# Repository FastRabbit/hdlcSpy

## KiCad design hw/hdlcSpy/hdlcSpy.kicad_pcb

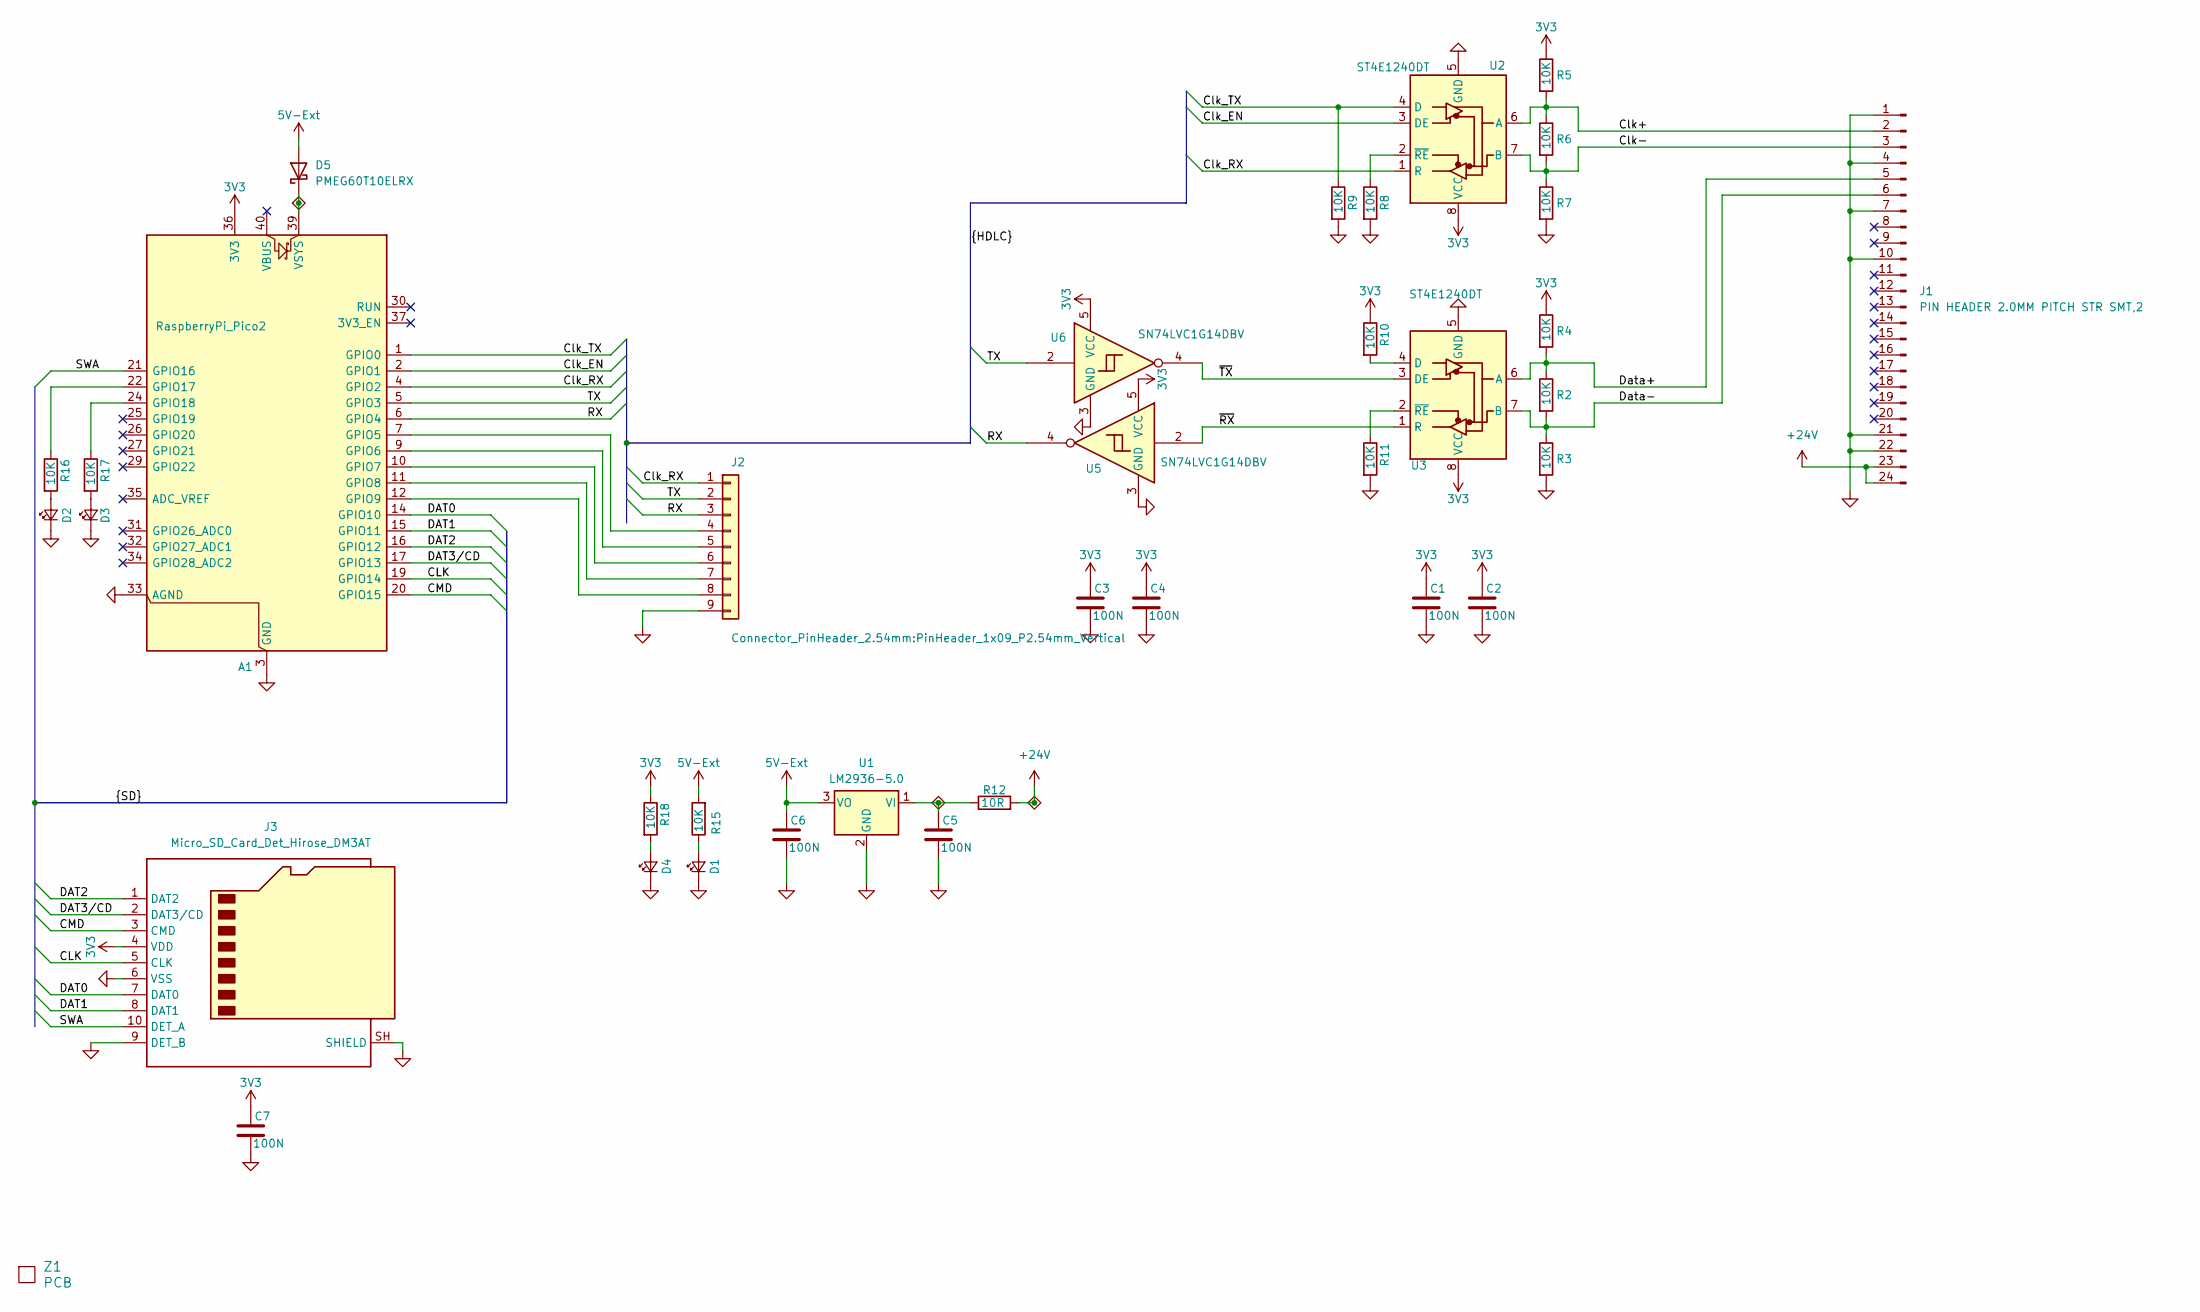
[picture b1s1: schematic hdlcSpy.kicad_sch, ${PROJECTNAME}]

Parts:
A1: RaspberryPi_Pico2; RaspberryPi_Pico_Common_Unspecified; DigiKey 2648-SC1631CT-ND
C1, C2, C3, C4, C5, C6, C7: 100N; C_0603_1608Metric_Pad1.08x0.95mm_HandSolder
D1, D2, D3, D4: VLMTG1400-GS08; LED_0603_1608Metric; DigiKey VLMTG1400-GS08CT-ND
D5: PMEG60T10ELRX; Nexperia_CFP3_SOD-123W; DigiKey 1727-7807-1-ND
J1: PIN HEADER 2.0MM PITCH STR SMT,2; G825M24401YEU; DigiKey 664-G825M24401YEUTR-ND
J2: Connector_PinHeader_2.54mm:PinHeader_1x09_P2.54mm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; PinHeader_1x09_P2.54mm_Vertical
J3: Micro_SD_Card_Det_Hirose_DM3AT; DM3CS-SF; Mouser 798-DM3D-SF
R2, R3, R4, R5, R6, R7, R8, R9, R10, R11, R15, R16, R17, R18: 10K; R_0603_1608Metric_Pad0.98x0.95mm_HandSolder
R12: 10R; R_0603_1608Metric_Pad0.98x0.95mm_HandSolder
U1: LM2936-5.0; SOT-223-3_TabPin2; DigiKey LM2936MP-5.0/NOPBCT-ND
U2, U3: ST4E1240DT; SOIC-8_3.9x4.9mm_P1.27mm; DigiKey 296-23802-1-ND
U5, U6: SN74LVC1G14DBV; SOT-23-5; DigiKey 296-11607-1-ND
Z1: PCB; 4L

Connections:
3V3: A1.36 (3V3), C1.1, C2.1, C3.1, C4.1, C7.1, J3.4 (VDD), R4.1, R5.1, R10.1, R18.1, U2.8 (VCC), U3.8 (VCC), U5.5 (VCC), U6.5 (VCC)
5V-Ext: C6.1, D5.2 (A), R15.2, U1.3 (VO)
+24V: J1.23, J1.24, R12.2
/CLK: A1.19 (GPIO14), J3.5 (CLK)
/CMD: A1.20 (GPIO15), J3.3 (CMD)
/Clk+: J1.2, R5.2, R6.1, U2.6 (A)
/Clk-: J1.3, R6.2, R7.1, U2.7 (B)
/Clk_EN: A1.2 (GPIO1), U2.3 (DE)
/Clk_RX: A1.4 (GPIO2), J2.1, U2.1 (R)
/Clk_TX: A1.1 (GPIO0), R9.1, U2.4 (D)
/DAT0: A1.14 (GPIO10), J3.7 (DAT0)
/DAT1: A1.15 (GPIO11), J3.8 (DAT1)
/DAT2: A1.16 (GPIO12), J3.1 (DAT2)
/DAT3/CD: A1.17 (GPIO13), J3.2 (DAT3/CD)
/Data+: J1.5, R2.1, R4.2, U3.6 (A)
/Data-: J1.6, R2.2, R3.1, U3.7 (B)
/RX: A1.6 (GPIO4), J2.3, U5.4
/SWA: A1.21 (GPIO16), J3.10 (DET_A)
/TX: A1.5 (GPIO3), J2.2, U6.2
/~RX: U3.1 (R), U5.2
/~TX: U3.3 (DE), U6.4
GND: A1.3 (GND), A1.8 (GND), A1.13 (GND), A1.18 (GND), A1.23 (GND), A1.28 (GND), A1.33 (AGND), A1.38 (GND), C1.2, C2.2, C3.2, C4.2, C5.2, C6.2, C7.2, D1.1 (K), D2.1 (K), D3.1 (K), D4.1 (K), J1.1, J1.4, J1.7, J1.10, J1.21, J1.22, J2.9, J3.6 (VSS), J3.9 (DET_B), J3.SH (SHIELD), R3.2, R7.2, R8.2, R9.2, R11.2, U1.2 (GND), U2.5 (GND), U3.5 (GND), U5.3 (GND), U6.3 (GND)
unnamed: A1.7 (GPIO5), J2.4
unnamed: A1.9 (GPIO6), J2.5
unnamed: A1.10 (GPIO7), J2.6
unnamed: A1.11 (GPIO8), J2.7
unnamed: A1.12 (GPIO9), J2.8
unnamed: A1.22 (GPIO17), R16.1
unnamed: A1.24 (GPIO18), R17.1
unnamed: A1.39 (VSYS), D5.1 (K)
unnamed: D1.2 (A), R15.1
unnamed: D2.2 (A), R16.2
unnamed: D3.2 (A), R17.2
unnamed: D4.2 (A), R18.2
unnamed: C5.1, R12.1, U1.1 (VI)
unnamed: R8.1, U2.2 (~RE)
unnamed: R10.2, U3.4 (D)
unnamed: R11.1, U3.2 (~RE)

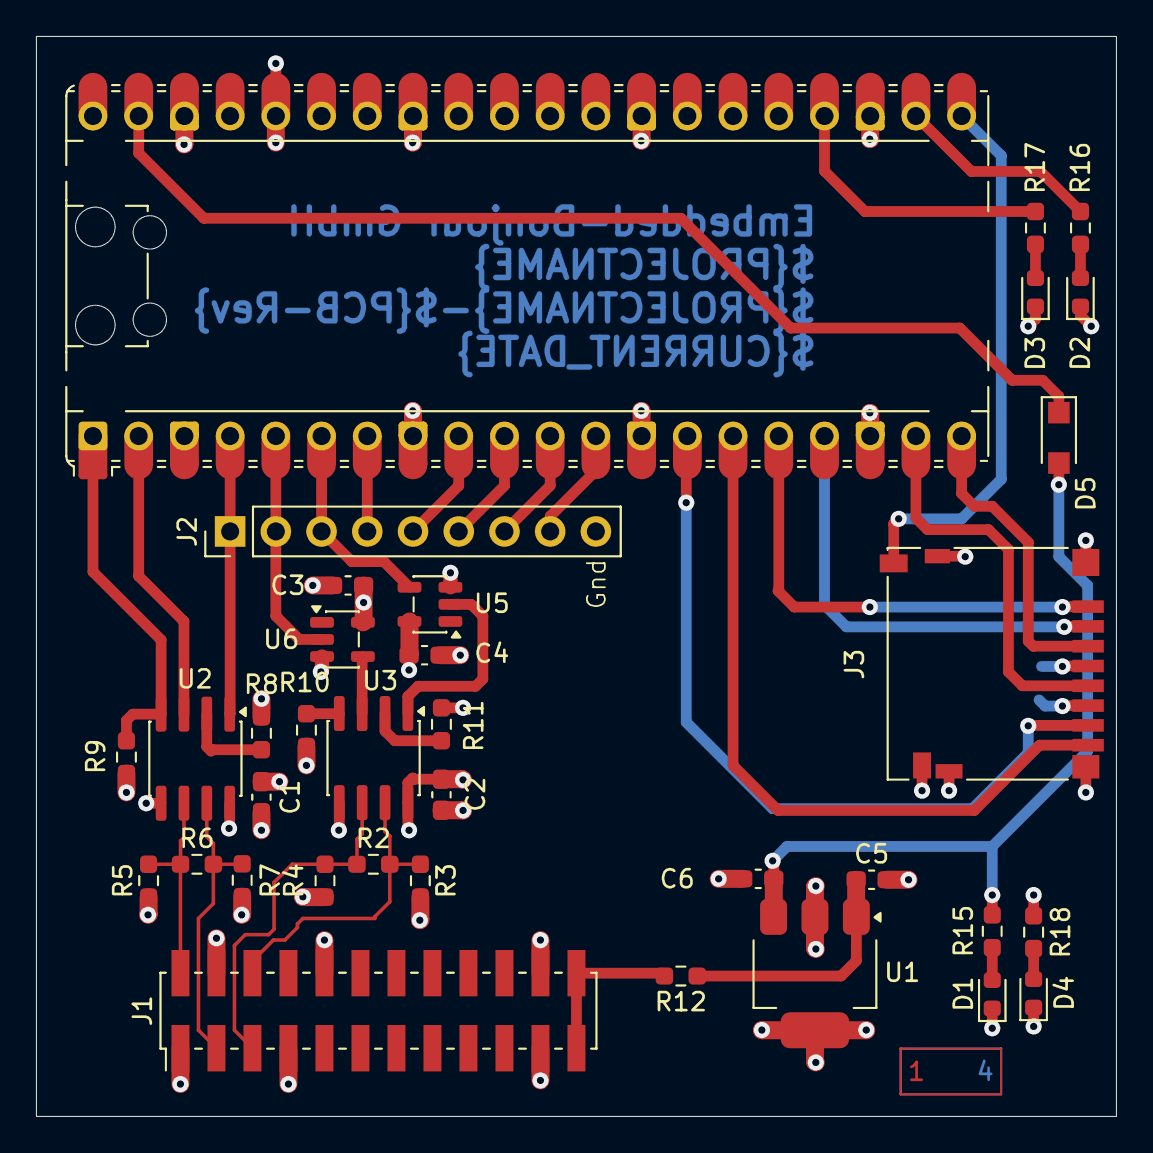
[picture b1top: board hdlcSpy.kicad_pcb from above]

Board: 4 copper layers, 60.0 x 60.0 mm, 37 parts (1 on the bottom side), 38 nets.

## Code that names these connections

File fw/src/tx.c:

#include "tx.h"

#include "hardware/clocks.h"
#include "hardware/gpio.h"
#include "sys.h"
#include "tx_clock.h"
#include <pico/types.h>
#include <stdbool.h>
#include <stdint.h>

/*
    GPIO0 Clk Tx        Out
    GPIO1 Enable Tx     Out
    GPIO2 Clk Rx        In
    GPIO3 Data Tx       Out
    GPIO4 Data Rx       In
*/

/*
    TX 0    Driver Disable   Bus Low
    TX 1    Driver Enable   Bus High
 */

const uint8_t rx_clock_pin = 2u;
const uint8_t tx_pin = 3u;
const uint8_t rx_pin = 4u;

const uint16_t hdlc_flag = 0x007E;
const uint16_t hdlc_abort = 0x00FF;
const uint16_t hdlc_idle = 0x03FF;

typedef struct {
    bool tx_inverted;
} tx_state_t;

static tx_state_t tx_state = {
    .tx_inverted = false,
};

void tx_driver_init(void) {
    gpio_init(tx_pin);
    gpio_set_dir(tx_pin, GPIO_OUT);
    gpio_put(tx_pin, 1u);
    gpio_init(rx_clock_pin);
    gpio_set_dir(rx_clock_pin, GPIO_IN);
}

void wait_clk_edge(bool high) {
    while (gpio_get(rx_clock_pin) != (high ? 1u : 0u)) {
        tight_loop_contents();
    }
}

void tx_send_bit(uint8_t bit) {
    wait_clk_edge(true);
    if (tx_state.tx_inverted) {
        gpio_put(tx_pin, bit ? 0u : 1u);
    } else {
        gpio_put(tx_pin, bit ? 1u : 0u);
    }
    wait_clk_edge(false);
}

void tx_send_byte(uint8_t byte, bool bit_stuff) {
    uint8_t bit_stuff_cnt = 0u;
    uint8_t bit_mask = 0x01u;
    DEB(8, true);
    for (uint_fast8_t i = 0u; i < 8u; i++) {
        uint8_t bit = (byte & bit_mask) ? 1u : 0u;
        if (bit_stuff) {
            if (bit) {
                bit_stuff_cnt++;
                if (bit_stuff_cnt > 5u) {
                    DEB(9, true);
                    tx_send_bit(0u);
                    bit_stuff_cnt = 0u;
                    DEB(9, false);
                }
            } else {
                bit_stuff_cnt = 0u;
            }
        }
        tx_send_bit(bit);
        bit_mask <<= 1u;
    }
    DEB(8, false);
}

void tx_cmd(uint16_t data, uint8_t length) {
    uint16_t bit_mask = 0x0001u;
    for (uint_fast8_t i = 0u; i < length; i++) {
        uint8_t bit = (data & bit_mask) ? 1u : 0u;
        tx_send_bit(bit);
        bit_mask <<= 1u;
    }
}

void tx_send(uint8_t data, uint32_t count, bool bit_stuff) {

    for (uint32_t loop = 0; loop < count; loop++) {
        tx_send_byte(data, bit_stuff);
    }
}

void send_frame(uint16_t length, uint8_t data) {
    tx_cmd(hdlc_flag, 8);
    for(uint_fast16_t i=0; i<length; i++) {
       tx_send(data, 1, true);
    }
    tx_cmd(hdlc_flag, 8);
}

static int cmd_tx_abort(cli_t *cli, const cli_args_t *args, void *user) {
    (void)cli; (void)args; (void)user;
    tx_cmd(hdlc_abort, 8);
    return 0;
}

static int cmd_tx_flag(cli_t *cli, const cli_args_t *args, void *user) {
    (void)cli; (void)args; (void)user;
    tx_cmd(hdlc_flag, 8);
    return 0;
}

static int cmd_tx_send(cli_t *cli, const cli_args_t *args, void *user) {
    (void)cli; (void)user;
    uint8_t data = (uint8_t) cli_arg_uint(args, 0, 0);
    uint32_t count = (uint32_t) cli_arg_uint(args, 1, 1);
    tx_send(data, count, true);
    return 0;
}

static int cmd_tx(cli_t *cli, const cli_args_t *args, void *user) {
    (void)args; (void)user;
    cli_printf(cli, "tx: inverte=%s \n", tx_state.tx_inverted ? "on" : "off");
    return 0;
}

static int cmd_tx_invert(cli_t *cli, const cli_args_t *args, void *user) {
    (void)cli; (void)user;
    tx_state.tx_inverted = cli_arg_bool(args, 0u, false);
    return 0;
}

static int cmd_tx_frame(cli_t *cli, const cli_args_t *args, void *user) {
    (void)cli; (void)user;
    uint16_t length = (uint16_t) cli_arg_uint(args, 0, 0);
    uint8_t data = (uint8_t) cli_arg_uint(args, 1, 0);
    uint32_t count = cli_arg_uint(args, 2, 1);
    while(count--) {
        send_frame(length, data);
        tx_cmd(hdlc_idle, 10);
    }
    return 0;
}

static const cli_arg_spec_t tx_set_args[] = {
    { "state", CLI_ARG_BOOL, false, false, NULL, "on/off, true/false, yes/no, 1/0" },
};

static const cli_arg_spec_t tx_send_args[] = {
    { "data", CLI_ARG_UINT, false, false, NULL, "data byte to send 0..255" },
    { "count", CLI_ARG_UINT, true, false, NULL, "number of repeats, default to 1"},
};

static const cli_arg_spec_t tx_frame_args[] = {
    { "length", CLI_ARG_UINT, false, false, NULL, "frame lenght"},
    { "data", CLI_ARG_UINT, false, false, NULL, "data to send 0..255" },
    { "count", CLI_ARG_UINT, true, false, NULL, "number of repeats, default to 1"},
};

static const cli_cmd_t tx_subs[] = {
    { "abort", "send the HDLC Abort ", NULL, 0u, NULL, 0u, cmd_tx_abort },
    { "flag", "send the HDLC Flag 0x7E", NULL, 0u, NULL, 0u, cmd_tx_flag },
    { "send", "send a byte over TX", NULL, 0u, tx_send_args, 2u, cmd_tx_send },
    { "invert", "invert TX",  NULL, 0u, tx_set_args, 1u, cmd_tx_invert },
    { "frame", "send frame",  NULL, 0u, tx_frame_args, 3u, cmd_tx_frame },
};

const cli_cmd_t tx_cli_command = {
    "tx", "TX bit bang commands", tx_subs,
    sizeof(tx_subs) / sizeof(tx_subs[0]), NULL, 0u, cmd_tx
};
